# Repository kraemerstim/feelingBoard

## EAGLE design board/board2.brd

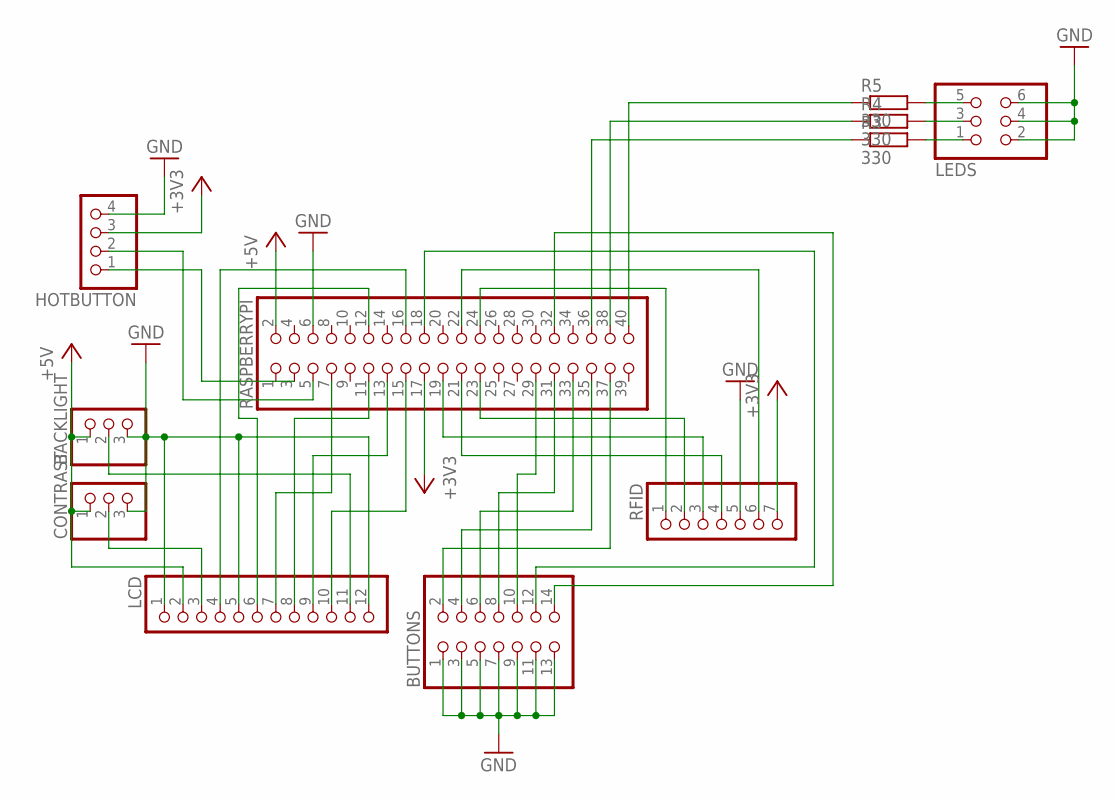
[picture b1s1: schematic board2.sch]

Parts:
BACKLIGHT: PINHD-1X3; 1X03
BUTTONS: PINHD-2X7; 2X07
CONTRAST: PINHD-1X3; 1X03
HOTBUTTON: PINHD-1X4; 1X04
LCD: PINHD-1X12; 1X12
LEDS: PINHD-2X3; 2X03
R3, R4, R5: 330; 0207/10
RASPBERRYPI: PINHD-2X20; 2X20
RFID: PINHD-1X7; 1X07

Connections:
+3V3: HOTBUTTON.3, RASPBERRYPI.17, RFID.7
+5V: BACKLIGHT.1, CONTRAST.1, LCD.2, RASPBERRYPI.2
GND: BACKLIGHT.3, BUTTONS.1, BUTTONS.3, BUTTONS.5, BUTTONS.7, BUTTONS.9, BUTTONS.11, BUTTONS.13, CONTRAST.3, HOTBUTTON.4, LCD.1, LCD.5, LCD.12, LEDS.2, LEDS.4, LEDS.6, RASPBERRYPI.6, RFID.5
unnamed: RASPBERRYPI.22, RFID.6
unnamed: RASPBERRYPI.24, RFID.1
unnamed: RASPBERRYPI.23, RFID.2
unnamed: RASPBERRYPI.19, RFID.3
unnamed: RASPBERRYPI.21, RFID.4
unnamed: CONTRAST.2, LCD.3
unnamed: BACKLIGHT.2, LCD.11
unnamed: BUTTONS.2, RASPBERRYPI.37
unnamed: BUTTONS.4, RASPBERRYPI.35
unnamed: LCD.4, RASPBERRYPI.16
unnamed: LCD.6, RASPBERRYPI.12
unnamed: LCD.7, RASPBERRYPI.7
unnamed: LCD.8, RASPBERRYPI.11
unnamed: LCD.9, RASPBERRYPI.13
unnamed: LCD.10, RASPBERRYPI.15
unnamed: BUTTONS.8, RASPBERRYPI.31
unnamed: BUTTONS.10, RASPBERRYPI.29
unnamed: BUTTONS.12, RASPBERRYPI.18
unnamed: BUTTONS.14, RASPBERRYPI.32
unnamed: LEDS.5, R5.2
unnamed: LEDS.3, R4.2
unnamed: LEDS.1, R3.2
unnamed: R5.1, RASPBERRYPI.40
unnamed: R4.1, RASPBERRYPI.38
unnamed: R3.1, RASPBERRYPI.36
unnamed: HOTBUTTON.1, RASPBERRYPI.3
unnamed: HOTBUTTON.2, RASPBERRYPI.5
unnamed: BUTTONS.6, RASPBERRYPI.33

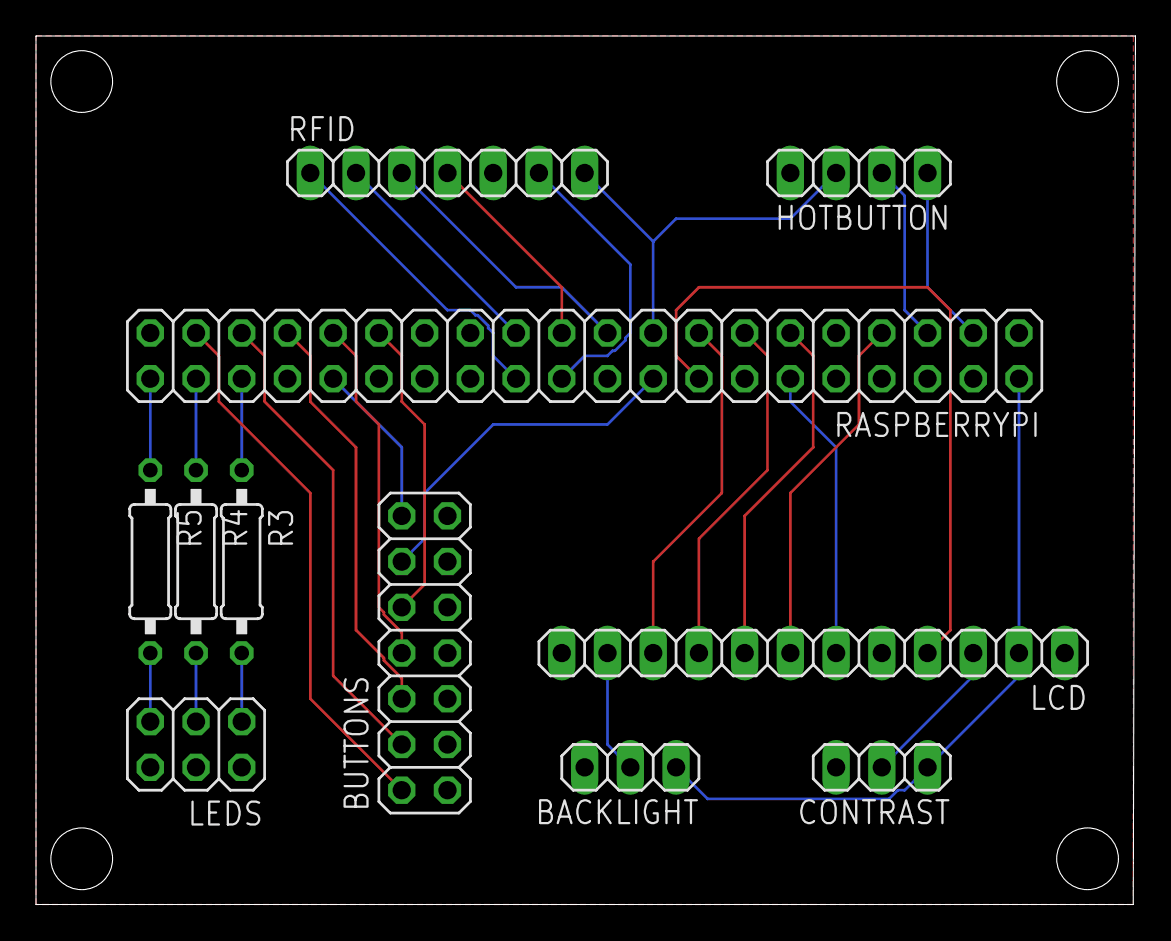
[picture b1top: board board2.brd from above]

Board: 2 copper layers, 61.1 x 48.3 mm, 11 parts (0 on the bottom side), 31 nets.

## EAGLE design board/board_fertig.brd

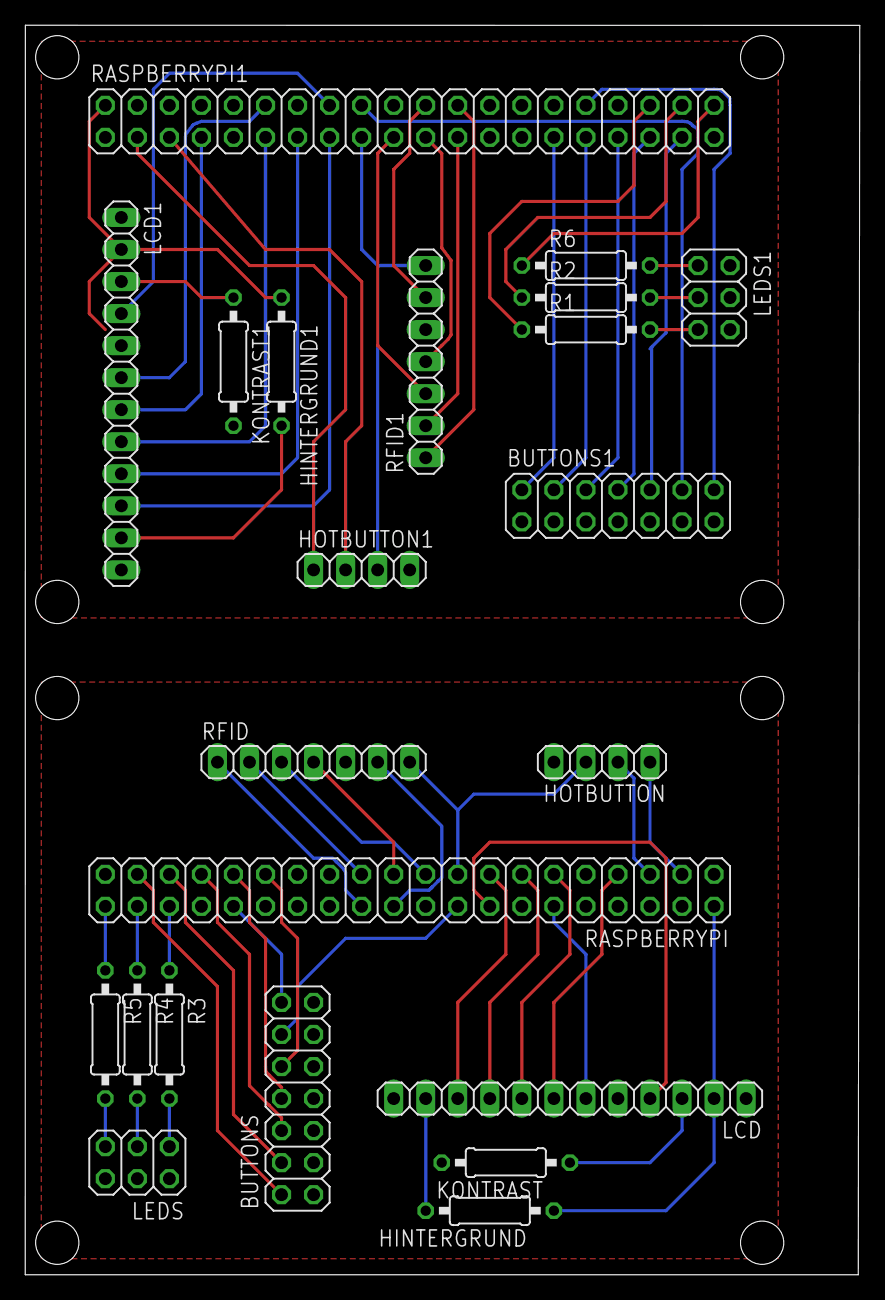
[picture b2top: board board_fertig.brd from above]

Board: 2 copper layers, 66.2 x 99.1 mm, 22 parts (0 on the bottom side), 62 nets.

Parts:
BUTTONS, BUTTONS1: 2X07
HINTERGRUND, HINTERGRUND1: 0207/10
HOTBUTTON, HOTBUTTON1: 1X04
KONTRAST, KONTRAST1: 0207/10
LCD, LCD1: 1X12
LEDS, LEDS1: 2X03
R1, R2, R3, R4, R5, R6: 330; 0207/10
RASPBERRYPI, RASPBERRYPI1: 2X20
RFID, RFID1: 1X07

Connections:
+3V1: HOTBUTTON1.3, RASPBERRYPI1.17, RFID1.7
+3V3: HOTBUTTON.3, RASPBERRYPI.17, RFID.7
+5V: HINTERGRUND.1, LCD.2, RASPBERRYPI.2
+5V1: HINTERGRUND1.1, LCD1.2, RASPBERRYPI1.2
GND: BUTTONS.1, BUTTONS.3, BUTTONS.5, BUTTONS.7, BUTTONS.9, BUTTONS.11, BUTTONS.13, HOTBUTTON.4, KONTRAST.2, LCD.1, LCD.5, LCD.12, LEDS.2, LEDS.4, LEDS.6, RASPBERRYPI.6, RFID.5
GND1: BUTTONS1.1, BUTTONS1.3, BUTTONS1.5, BUTTONS1.7, BUTTONS1.9, BUTTONS1.11, BUTTONS1.13, HOTBUTTON1.4, KONTRAST1.2, LCD1.1, LCD1.5, LCD1.12, LEDS1.2, LEDS1.4, LEDS1.6, RASPBERRYPI1.6, RFID1.5
unnamed: RASPBERRYPI.22, RFID.6
unnamed: RASPBERRYPI.24, RFID.1
unnamed: RASPBERRYPI.23, RFID.2
unnamed: RASPBERRYPI.19, RFID.3
unnamed: RASPBERRYPI.21, RFID.4
unnamed: KONTRAST.1, LCD.3
unnamed: HINTERGRUND.2, LCD.11
unnamed: BUTTONS.2, RASPBERRYPI.37
unnamed: BUTTONS.4, RASPBERRYPI.35
unnamed: RASPBERRYPI1.22, RFID1.6
unnamed: LCD.4, RASPBERRYPI.16
unnamed: LCD.6, RASPBERRYPI.12
unnamed: LCD.7, RASPBERRYPI.7
unnamed: LCD.8, RASPBERRYPI.11
unnamed: LCD.9, RASPBERRYPI.13
unnamed: LCD.10, RASPBERRYPI.15
unnamed: BUTTONS.8, RASPBERRYPI.31
unnamed: BUTTONS.10, RASPBERRYPI.29
unnamed: BUTTONS.12, RASPBERRYPI.18
unnamed: BUTTONS.14, RASPBERRYPI.32
unnamed: LEDS.5, R5.2
unnamed: LEDS.3, R4.2
unnamed: LEDS.1, R3.2
unnamed: R5.1, RASPBERRYPI.40
unnamed: R4.1, RASPBERRYPI.38
unnamed: R3.1, RASPBERRYPI.36
unnamed: HOTBUTTON.1, RASPBERRYPI.3
unnamed: HOTBUTTON.2, RASPBERRYPI.5
unnamed: BUTTONS.6, RASPBERRYPI.33
unnamed: RASPBERRYPI1.24, RFID1.1
unnamed: RASPBERRYPI1.23, RFID1.2
unnamed: RASPBERRYPI1.19, RFID1.3
unnamed: RASPBERRYPI1.21, RFID1.4
unnamed: LCD1.4, RASPBERRYPI1.16
unnamed: LCD1.7, RASPBERRYPI1.7
unnamed: LCD1.8, RASPBERRYPI1.11
unnamed: LCD1.9, RASPBERRYPI1.13
unnamed: LCD1.10, RASPBERRYPI1.15
unnamed: BUTTONS1.2, RASPBERRYPI1.29
unnamed: BUTTONS1.4, RASPBERRYPI1.31
unnamed: BUTTONS1.6, RASPBERRYPI1.33
unnamed: BUTTONS1.8, RASPBERRYPI1.35
unnamed: BUTTONS1.10, RASPBERRYPI1.37
unnamed: BUTTONS1.12, RASPBERRYPI1.18
unnamed: BUTTONS1.14, RASPBERRYPI1.32
unnamed: R6.1, RASPBERRYPI1.40
unnamed: R2.1, RASPBERRYPI1.38
unnamed: R1.1, RASPBERRYPI1.36
unnamed: LCD1.6, RASPBERRYPI1.12
unnamed: HOTBUTTON1.1, RASPBERRYPI1.3
unnamed: HOTBUTTON1.2, RASPBERRYPI1.5
unnamed: LEDS1.5, R1.2
unnamed: LEDS1.3, R2.2
unnamed: LEDS1.1, R6.2
unnamed: KONTRAST1.1, LCD1.3
unnamed: HINTERGRUND1.2, LCD1.11

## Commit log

2017-09-20 spring-boot-app hinzugefügt
2017-09-20 feeling_machine und start auseinandergezogen und in Klassen geändert
    display hat jetzt eine Zeitangabe
    tabs einheitlich gemacht
2017-09-20 gitignore hinzugefügt
2017-09-21 einrückungen vereinheitlicht
2017-09-22 laufschrift implementiert
2017-09-22 display + laufschrift repariert
2017-09-23 Kleinere Bugfixes am Display, Einbinden von Chart.js
2017-09-24 Anzeige des Diagramms verbessert
2017-09-25 Chart-update mit Ajax
2017-09-26 Tests mit Slider
2017-09-27 Slider gone -> Date-Picker ist da!
2017-10-01 Auslagern von Status und UserMode
2017-10-01 AjaxFetch gibt alle accounts zurück
2017-10-01 soundMode erstellt, LED verschoben
2017-10-02 Kleinere Bugfixes
2017-10-02 bootstrap slider entfernt
2017-10-03 Resolves #1
2017-10-03 Kurze Pause vor Shutdown/Restart eingebaut
2017-10-07 random Sounds implementiert
2017-10-13 tests entfernt
2017-10-15 Rest-Timeout erhöht und Sound-Pfade in absolute Pfade transformiert
    + Sounds eingecheckt
2017-10-19 Adminmode geändert (links rechts + auswahl) Update-funktionalität implementiert
2017-10-19 kleinerer Bugfix
2017-10-19 nach applyConfig wird das display nicht mehr resetted
2017-10-22 Sounds umbenannt
2017-10-22 Initialisierung display/status aus feeling_machine nach start verlagert
2017-10-25 Anfang Benutzersensitive Webseite
2017-10-31 configReader implementiert Anzeige verbessert
2017-10-31 minor bugfix
2017-10-31 Spring Security Probleme beseitigt
2017-11-01 spring-probleme beseitigt #2
2017-11-01 ids für account-abfrage hinzugefügt
2017-11-01 Restkey wurde eingebaut
2017-11-05 feeling_IO eingeführt - configReader eingefügt
2017-11-05 Display in feeling_IO verlagert
2017-11-05 RFID-Reader in feelingIO verlagert
2017-11-05 Sound in feeling_IO verlagert
2017-11-05 Buttons ausgelagert
2017-11-05 minor bugfixes
2017-11-06 index des channels anstatt channel übertragen
2017-11-07 EntryReturnData eingefügt um die Rückgabewerte zu definieren
2017-11-08 demo-kommentare entfernen
2017-11-08 Team ausgelagert, Code-registrierung verbessert
2017-11-12 Viele Anpassungen - Passwort wird gehasht - Registrieren und Login - Chart kann nur von angemeldetem Benutzer angeschaut werden
2017-11-12 es wird ein code erstellt wenn der account abgefragt wird
2017-11-12 Bugfixes und Codeausgabe
2017-11-12 testmode entfernt
2017-11-13 Kleinere Bugfixes und es wird nurnoch anonym und eigene daten angezeigt
    Solves #7
2017-11-13 Modes werden klein geschrieben
2017-11-13 Sounds werden über absolute Pfade abgespielt
2017-11-13 bugfix schreibfehler
2017-11-13 hoert nicht auf...
2017-11-13 hoffentlich letzter bugfix heute
2017-11-13 jetzt aber
2017-11-13 naechster versuch
2017-11-14 bugfixes tag 1: Code wird nicht nochmal generiert Zu schnelles drücken blockiert das Display nicht Anton -> Felix
2017-11-14 Der Anzeigename kann eingestellt werden Register und Kontakt geben nun nette Meldungen aus
2017-11-16 Create LICENSE
2017-11-16 Erfolgsmeldungen Grün gemacht und keine formulare mehr angezeigt
    solves #9
2017-11-16 Beim Registrieren des Accounts muss der Code gelöscht werden
    Fixes #10
2017-11-16 Es werden jetzt im Chart Labels anstatt Zahlen angezeigt
    Closes #12
2017-11-16 Hauptseite etwas erweitert (kleiner Schritt in Richtung #13)
2017-11-17 Feelings wurden umgekehrt (0 = schlecht, 5 = super) Resolves #18
2017-11-17 RFID-Erkennung-Sustain auf 4 Sekunden erhöhen
    Closes #15
2017-11-17 Default heißt jetzt überall Kevin
2017-11-17 Chart lässt sich nicht mehr mit Datum filtern
    Resolves #16
2017-11-18 Feelings sind double, anonyme daten als bargraph anzeigen test.html eingerichtet
2017-11-19 Chart auf Bars ausgerichtet unnötiges entfernt
2017-11-22 Chart wird jetzt auf Tage gerundet
2017-11-22 Erster Draft für Teams
2017-11-23 Teams werden erstellt und wenn es kein mitglied mehr gibt gelöscht
2017-11-24 Es werden jetzt Teams im Chart angezeigt, und ChipIDs werden gehasht fixes #17
2017-11-25 Chart-controller aufgeräumt und Filterung nach Datum entfernt
2017-11-25 Bessere ausgliederung von Web-relevanten Klassen
2017-11-25 ReturnData in RestReturnData umbenannt
2017-11-25 Register/Login/Logout ausgelagert
2017-11-25 EntryInput in EntryRestInput umbenannt
2017-11-25 AccountRestReturnData gibt für das Team nur den Namen zurück
2017-11-26 Bugfixes und auslagerung der hipchat/feelingboard-url
2017-11-30 Anpassung der GPIO-Pins
2017-12-03 Set GPIO-Mode to bcm at start
2018-01-02 Display-Reset eingeführt
2018-01-02 Umstellung auf 4 Buttons
2018-01-02 usermode auf 4 buttons umgestellt
2018-01-16 Aendern des charts auf 4 Buttons
2018-02-23 Anpassung der Pins auf die Platine
2018-02-23 Anfang Achievement
2018-03-06 Achievements und Verschiedene Anpassungen / Bugfixes
    - Achievements werden jetzt berücksichtigt (Spring + Python)
    - Anzeige von Kalenderwoche/Monat angepasst
    - Buttons an Board angepasst
    - Refactoring der Package/Class/Variablen-Namen
2018-03-06 Bugfix: package-name geändert
2018-03-18 Initial commit Milestones
2018-03-18 Application.properties and config.ini are now checked in as an example-file
    jars are not checked in
2018-03-25 removed unneeded maven files
2018-03-25 Renamed restkey and implemented it for getting/posting entries
2018-04-22 resolves #23
2018-04-28 resolves #23 strategy for id-field changed from auto to identity
2019-02-08 Box eingecheckt
2020-01-03 Pinbelegung und Platinen-Dateien eingecheckt
2024-07-30 Bump org.webjars:bootstrap from 3.3.7 to 3.4.0 in /springBoot
    Bumps [org.webjars:bootstrap](https://github.com/webjars/bootstrap) from 3.3.7 to 3.4.0.
    - [Commits](https://github.com/webjars/bootstrap/compare/bootstrap-3.3.7...bootstrap-3.4.0)
    ---
    updated-dependencies:
    - dependency-name: org.webjars:bootstrap
    dependency-type: direct:production
2024-08-01 Bump org.webjars:bootstrap from 3.3.7 to 3.4.1 in /springBoot
    Bumps [org.webjars:bootstrap](https://github.com/webjars/bootstrap) from 3.3.7 to 3.4.1.
    - [Commits](https://github.com/webjars/bootstrap/compare/bootstrap-3.3.7...bootstrap-3.4.1)
    ---
    updated-dependencies:
    - dependency-name: org.webjars:bootstrap
    dependency-type: direct:production
